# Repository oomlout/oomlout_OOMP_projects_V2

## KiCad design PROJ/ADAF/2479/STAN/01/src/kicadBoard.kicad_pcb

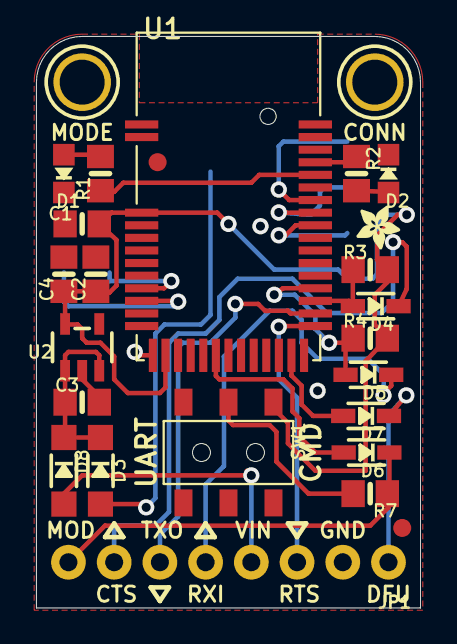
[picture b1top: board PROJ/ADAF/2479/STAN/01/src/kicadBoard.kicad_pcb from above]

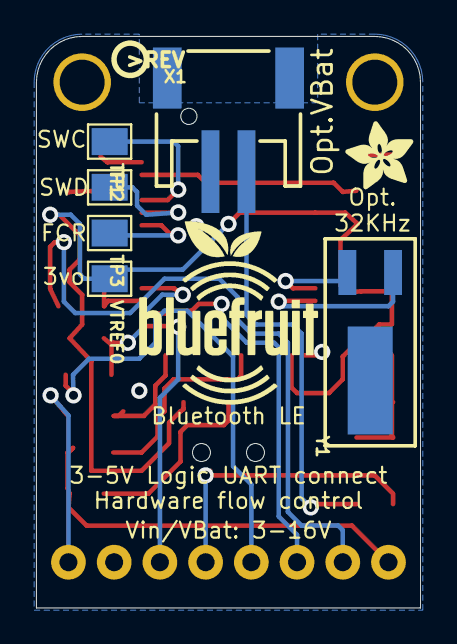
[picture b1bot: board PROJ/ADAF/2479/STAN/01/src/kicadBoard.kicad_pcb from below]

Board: 2 copper layers, 21.3 x 31.8 mm, 35 parts (9 on the bottom side), 25 nets.

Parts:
C1, C2: 1uF; 0805-NO
C3, C4: 10uF; 0805-NO
D1: RED; CHIPLED_0805_NOOUTLINE
D2: GREEN; CHIPLED_0805_NOOUTLINE
D3, D8: MBR120; SOD-123
D4, D5, D6, D7: 1n4148; SOD-323
FID1, FID2: FIDUCIAL""; FIDUCIAL_1MM
JP1: 1X08_ROUND_76
R1, R2: 1K; 0805-NO
R3, R4: 100K; 0805-NO
R7: 2K; 0805-NO
SW1: EG1319; EG1390
TP1: SWCLK; PAD-1.5X2.0
TP2: SWDIO; PAD-1.5X2.0
TP3: FCTRST; PAD-1.5X2.0
U1: BLE_MODULE_RAYTAC_MDBT40
U2: MIC5225-3.3; SOT23-5
U$9: BLUEFRUITLOGO_100MM
U$24: PCBFEAT-REV-040
U$25: ADAFRUIT_3.5MM
U$26: ADAFRUIT_2.5MM
U$28, U$29: MOUNTINGHOLE2.5; MOUNTINGHOLE_2.5_PLATED
VTREF0: FCTRST; PAD-1.5X2.0
X1: JST 2PH; JSTPH2
Y1: 32.768kHz (535-9166-2-ND); CRYSTAL_CYL_2X6MM_SMT

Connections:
3.3V: C1.1, C2.1, C4.1, R3.2, R4.2, SW1.O2, U1.3, U1.14, U2.5, VTREF0.P$1
CONNECTED_LED: R2.1, U1.39
CTS_3V: D4.A, R3.1, U1.28
CTS_5V: D4.C, JP1.7
DFU_3V: D7.A, U1.24
DFU_5V: D7.C, JP1.1
FCTRYRST_3V: TP3.P$1, U1.34
GND: C1.2, C2.2, C3.2, C4.2, D1.C, D2.C, JP1.2, SW1.S2, U1.1, U1.2, U1.13, U1.16, U1.25, U1.42, U2.2, X1.1
MODE_3V: D6.A, U1.18
MODE_5V: D6.C, JP1.8, R7.1
MODE_LED: R1.1, U1.38
unnamed: U1.9, Y1.1
unnamed: U1.10, Y1.2
unnamed: C3.1, D3.C, D8.C, U2.1, U2.3
unnamed: R7.2, SW1.P2
unnamed: D1.A, R1.2
unnamed: D2.A, R2.2
RTS_O: JP1.3, U1.26
RXD_3V: D5.A, R4.1, U1.29
RXD_5V: D5.C, JP1.5
SWCLK: TP1.P$1, U1.36
SWDIO/RST_3V: TP2.P$1, U1.35
TX_O: JP1.6, U1.27
VBAT: D3.A, X1.2
VIN: D8.A, JP1.4

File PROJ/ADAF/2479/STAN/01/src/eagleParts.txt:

Partlist

Exported from boardEagle.brd at 07/08/2022 18:05

EAGLE Version 9.6.2 Copyright (c) 1988-2020 Autodesk, Inc.

Assembly variant: 

Part     Value                     Package                  Library      Position (inch)       Orientation

C1       1uF                       0805-NO                  microbuilder (0.1 0.84)            R180
C2       1uF                       0805-NO                  microbuilder (0.13 0.73)           R90
C3       10uF                      0805-NO                  microbuilder (0.1 0.45)            R0
C4       10uF                      0805-NO                  microbuilder (0.06 0.73)           R90
D1       RED                       CHIPLED_0805_NOOUTLINE   microbuilder (0.06 0.95)           R180
D2       GREEN                     CHIPLED_0805_NOOUTLINE   microbuilder (0.77 0.95)           R0
D3       MBR120                    SOD-123                  microbuilder (0.14 0.3)            R270
D4       1n4148                    SOD-323                  microbuilder (0.742 0.66)          R180
D5       1n4148                    SOD-323                  microbuilder (0.726 0.51)          R180
D6       1n4148                    SOD-323                  microbuilder (0.722 0.34)          R180
D7       1n4148                    SOD-323                  microbuilder (0.721 0.42)          R180
D8       MBR120                    SOD-123                  microbuilder (0.06 0.3)            R270
FID1     FIDUCIAL""                FIDUCIAL_1MM             microbuilder (0.8 0.175)           R0
FID2     FIDUCIAL""                FIDUCIAL_1MM             microbuilder (0.265 0.975)         R0
JP1                                1X08_ROUND_76            microbuilder (0.42 0.1)            R180
R1       1K                        0805-NO                  microbuilder (0.14 0.95)           R90
R2       1K                        0805-NO                  microbuilder (0.7 0.95)            R270
R3       100K                      0805-NO                  microbuilder (0.73 0.74)           R0
R4       100K                      0805-NO                  microbuilder (0.73 0.59)           R0
R7       2K                        0805-NO                  microbuilder (0.73 0.25)           R180
SW1      EG1319                    EG1390                   microbuilder (0.42 0.34)           R180
TP1      SWCLK                     PAD-1.5X2.0              microbuilder (0.68 1.02)           MR270
TP2      SWDIO                     PAD-1.5X2.0              microbuilder (0.68 0.92)           MR90
TP3      FCTRST                    PAD-1.5X2.0              microbuilder (0.68 0.82)           MR270
U$28     MOUNTINGHOLE2.5           MOUNTINGHOLE_2.5_PLATED  microbuilder (0.74 1.15)           R0
U$29     MOUNTINGHOLE2.5           MOUNTINGHOLE_2.5_PLATED  microbuilder (0.1 1.15)            R0
U1                                 BLE_MODULE_RAYTAC_MDBT40 microbuilder (0.42 0.9)            R0
U2       MIC5225-3.3               SOT23-5                  microbuilder (0.1 0.57)            R0
VTREF    FCTRST                    PAD-1.5X2.0              microbuilder (0.68 0.72)           MR270
X1       JST 2PH                   JSTPH2                   microbuilder (0.42 1.1)            MR0
Y1       32.768kHz (535-9166-2-ND) CRYSTAL_CYL_2X6MM_SMT    microbuilder (0.11 0.65)           MR90

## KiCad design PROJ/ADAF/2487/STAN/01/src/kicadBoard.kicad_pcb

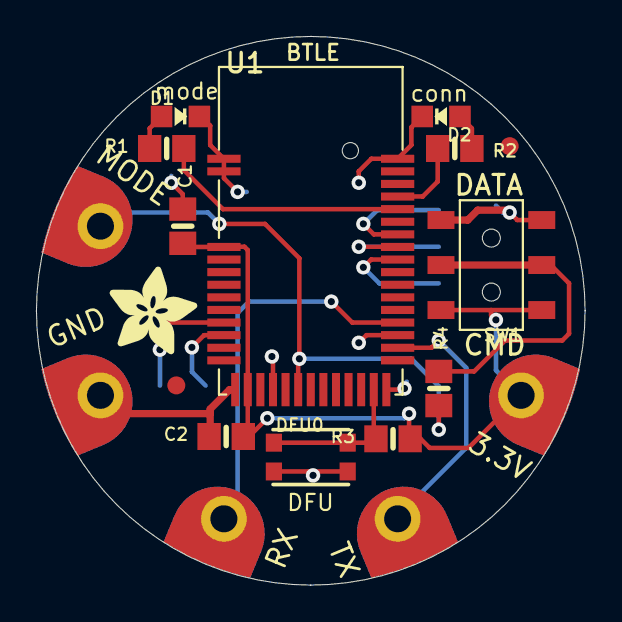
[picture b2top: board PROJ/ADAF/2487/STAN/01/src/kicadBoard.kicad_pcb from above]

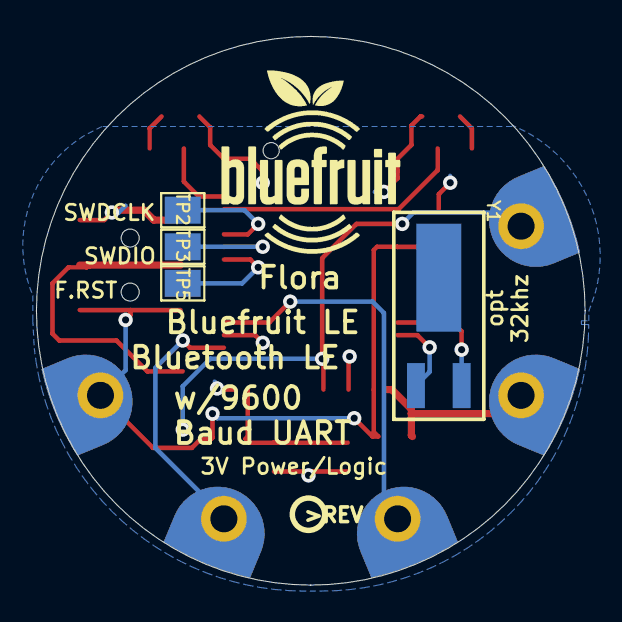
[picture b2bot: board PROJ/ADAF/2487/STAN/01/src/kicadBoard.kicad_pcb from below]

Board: 2 copper layers, 30.5 x 30.5 mm, 26 parts (7 on the bottom side), 16 nets.

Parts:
C1, C2: 1uF; 0805-NO
D1: RED; CHIPLED_0805_NOOUTLINE
D2: BLUE; CHIPLED_0805_NOOUTLINE
DFU0: KMR2; BTN_KMR2_4.6X2.8
FID1, FID2: FIDUCIAL""; FIDUCIAL_1MM
GND0: SEWTAP-2.0IN; SEWINGTAP_2.0
R1, R2, R4: 2K; 0805-NO
R3: 10K; 0805-NO
RX0: SEWTAP-2.0IN; SEWINGTAP_2.0
SW1: EG1319; EG1390
TP1: SEWTAP-2.0IN; SEWINGTAP_2.0
TP2: SWCLK; PAD-1.5X2.0
TP3: SWDIO; PAD-1.5X2.0
TP5: FCTRST; PAD-1.5X2.0
TX0: SEWTAP-2.0IN; SEWINGTAP_2.0
U1: MBT40; BLE_MODULE_RAYTAC_MDBT40
U$6: ADAFRUIT_5MM
U$7: FLORASMALL
U$23: BLUEFRUITLOGO_100MM
U$24: PCBFEAT-REV-040
UNK3V3IN0: SEWTAP-2.0IN; SEWINGTAP_2.0
Y1: 32.768kHz (535-9166-2-ND); CRYSTAL_CYL_2X6MM_SMT

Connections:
3.3V: C1.1, C2.1, R3.1, SW1.O1, SW1.O2, U1.3, U1.14, UNK3V3IN0.P$1
CONN_LED: R2.1, U1.39
DFU: DFU0.A, DFU0.A', R3.2, U1.24
FCTRYRST_3V: TP5.P$1, U1.34
GND: C1.2, C2.2, D1.C, D2.C, DFU0.B, DFU0.B', GND0.P$1, SW1.S1, SW1.S2, U1.1, U1.2, U1.13, U1.16, U1.25, U1.28, U1.42
MODE: R4.1, TP1.P$1, U1.18
MODE_LED: R1.1, U1.38
unnamed: R4.2, SW1.P1, SW1.P2
unnamed: D1.A, R1.2
unnamed: D2.A, R2.2
unnamed: U1.9, Y1.1
unnamed: U1.10, Y1.2
RXI: RX0.P$1, U1.29
SWCLK: TP2.P$1, U1.36
SWDIO/RST_3V: TP3.P$1, U1.35
TXO: TX0.P$1, U1.27

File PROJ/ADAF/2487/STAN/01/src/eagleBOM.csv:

"Part";"Value";"Device";"Package";"Description";"BOM";
"3V3IN";"SEWTAP-2.0IN";"SEWTAP-2.0IN";"SEWINGTAP_2.0";"";"";
"C1";"1uF";"CAP_CERAMIC0805-NOOUTLINE";"0805-NO";"Ceramic Capacitors";"";
"C2";"1uF";"CAP_CERAMIC0805-NOOUTLINE";"0805-NO";"Ceramic Capacitors";"";
"D1";"RED";"LED0805_NOOUTLINE";"CHIPLED_0805_NOOUTLINE";"LED";"";
"D2";"BLUE";"LED0805_NOOUTLINE";"CHIPLED_0805_NOOUTLINE";"LED";"";
"DFU";"KMR2";"SWITCH_TACT_SMT4.6X2.8";"BTN_KMR2_4.6X2.8";"SMT Tact Switches";"";
"FID1";"FIDUCIAL""";"FIDUCIAL""";"FIDUCIAL_1MM";"Fiducial Alignment Points";"EXCLUDE";
"FID2";"FIDUCIAL""";"FIDUCIAL""";"FIDUCIAL_1MM";"Fiducial Alignment Points";"EXCLUDE";
"GND";"SEWTAP-2.0IN";"SEWTAP-2.0IN";"SEWINGTAP_2.0";"";"";
"R1";"2K";"RESISTOR0805_NOOUTLINE";"0805-NO";"Resistors";"";
"R2";"2K";"RESISTOR0805_NOOUTLINE";"0805-NO";"Resistors";"";
"R3";"10K";"RESISTOR0805_NOOUTLINE";"0805-NO";"Resistors";"";
"R4";"2K";"RESISTOR0805_NOOUTLINE";"0805-NO";"Resistors";"";
"RX";"SEWTAP-2.0IN";"SEWTAP-2.0IN";"SEWINGTAP_2.0";"";"";
"SW1";"EG1319";"SWITCH_DPDTEG1390";"EG1390";"Switch - DPDT";"";
"TP1";"SEWTAP-2.0IN";"SEWTAP-2.0IN";"SEWINGTAP_2.0";"";"";
"TP2";"SWCLK";"TESTPOINT1.5X2.0MM_NOCREAM";"PAD-1.5X2.0";"Test Point";"";
"TP3";"SWDIO";"TESTPOINT1.5X2.0MM_NOCREAM";"PAD-1.5X2.0";"Test Point";"";
"TP5";"FCTRST";"TESTPOINT1.5X2.0MM_NOCREAM";"PAD-1.5X2.0";"Test Point";"";
"TX";"SEWTAP-2.0IN";"SEWTAP-2.0IN";"SEWINGTAP_2.0";"";"";
"U1";"MBT40";"NRF51822_MODULE_MDBT40";"BLE_MODULE_RAYTAC_MDBT40";"nRF51822 Bluetooth Low Energy Module";"";
"Y1";"32.768kHz (535-9166-2-ND)";"CRYSTAL2.0X6.0_32.768";"CRYSTAL_CYL_2X6MM_SMT";"Crystals";"";

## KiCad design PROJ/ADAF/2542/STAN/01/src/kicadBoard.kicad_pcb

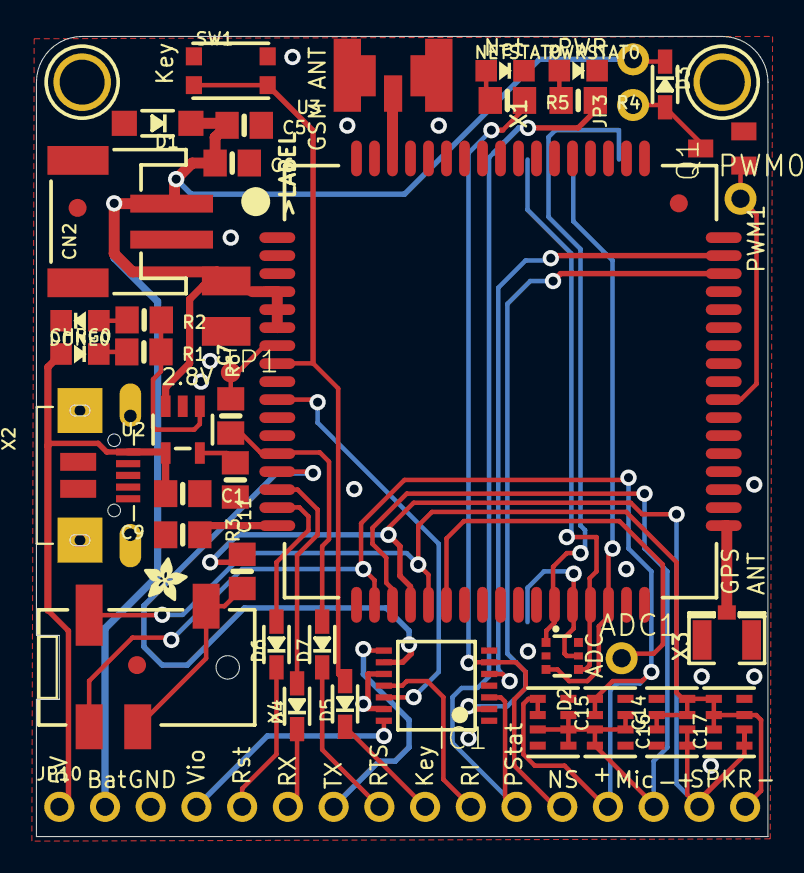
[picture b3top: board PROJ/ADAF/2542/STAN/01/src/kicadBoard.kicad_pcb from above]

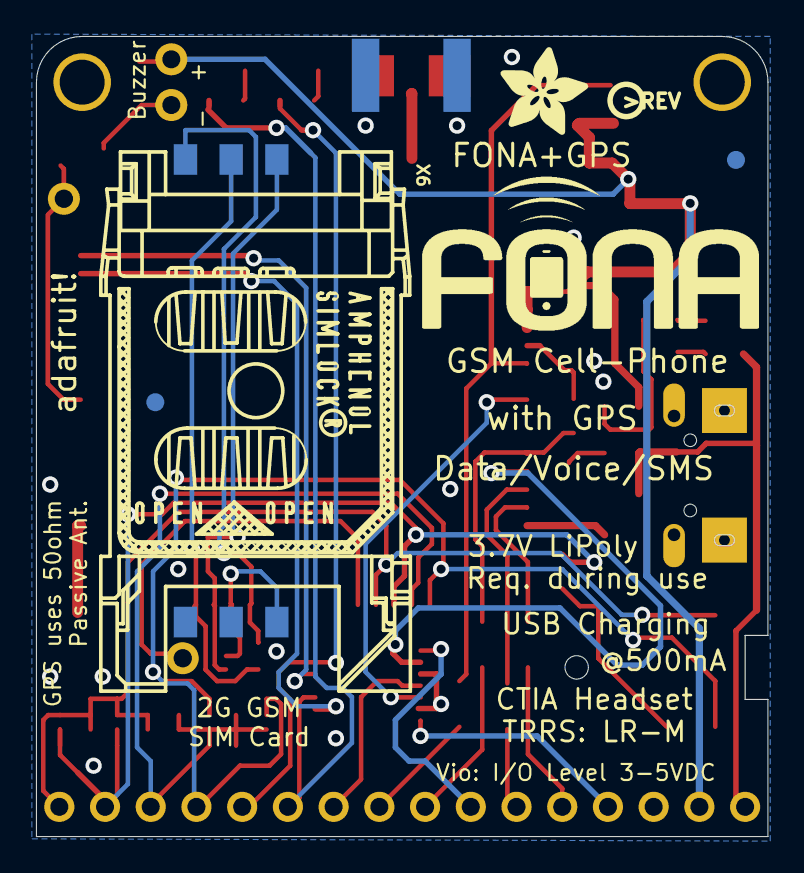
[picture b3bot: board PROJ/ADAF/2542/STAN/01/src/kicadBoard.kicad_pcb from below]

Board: 2 copper layers, 40.6 x 44.5 mm, 54 parts (6 on the bottom side), 42 nets.

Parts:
ADC1: 1X01-CLEANBIG
C1: 10µF; 0805-NO
C5: 10pF; 0805-NO
C6: 33pF; 0805-NO
C7: 100uF; C1210
C9, C11: 10uF; 0805-NO
C14, C16: 33pF; RESPACK_4X0603
C15, C17: 10pF; RESPACK_4X0603
CHRG0: ORANGE; CHIPLED_0805_NOOUTLINE
CN2: JSTPH; JSTPH2
D1: MMSZ5231BT1G; SOD-123
D2: SMF05C; SOT363
D3, D4, D5, D6, D7: 1N4148; SOD-323
DONE0: GREEN; CHIPLED_0805_NOOUTLINE
FID1, FID2, FID3, FID4, FID5: FIDUCIAL""; FIDUCIAL_1MM
IC1: 74VHCT125PW; TSSOP14
JP3: BUZZ; 1X02_ROUND
JP10: 1X16_ROUND
NETSTAT0: RED; CHIPLED_0805_NOOUTLINE
PWM0: 1X01-CLEANBIG
PWRSTAT0: BLUE; CHIPLED_0805_NOOUTLINE
Q1: DTC143ZUAT106; SC59-BEC
R1: 470; 0805-NO
R2, R4, R5: 1K; 0805-NO
R3: 2K; 0805-NO
R6: 10K; 0805-NO
SW1: KMR2; BTN_KMR2_4.6X2.8
TP1: TPTP11R; TP11R
U2: MCP73831T-2ACI/OT; SOT23-5
U3: SIM808; SIM900_SMT
U$21: ADAFRUIT_2.5MM
U$25: PCBFEAT-REV-040
U$26: FONA_LOGO
U$33, U$34: MOUNTINGHOLE2.5; MOUNTINGHOLE_2.5_PLATED
U$36: ADAFRUIT_5MM
X1: uFL; SMA_EDGELAUNCH_UFL
X2: MicroB; 4UCONN_20329
X3: uFL; U.FL
X4: 4UCONN_18510
X6: SIM_LOCKAMPHENOL; C707_10M006_512_2

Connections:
1.8V: D2.1, U3.P$29, X6.C1
2.8V: R6.2, TP1.TP, U3.P$7
+5V: C1.1, CHRG0.A, JP10.1, U2.4, X2.VBUS
GND: C1.2, C5.2, C6.2, C7.2, C9.2, C14.5, C14.8, C15.4, C15.8, C16.5, C16.8, C17.4, C17.8, CN2.1, D1.A, D2.2, DONE0.C, IC1.1, IC1.4, IC1.7, IC1.10, IC1.13, JP10.3, NETSTAT0.C, PWRSTAT0.C, Q1.E, R3.2, SW1.A, SW1.A', U2.2, U3.P$1, U3.P$2, U3.P$3, U3.P$18, U3.P$28, U3.P$34, U3.P$36, U3.P$40, U3.P$51, U3.P$52, U3.P$54, U3.P$64, U3.P$65, U3.P$67, U3.P$68, X1.GND@1, X1.GND@2, X1.GND@3, X1.GND@4, X2.BASE@1, X2.BASE@2, X2.GND, X2.SPRT@1, X2.SPRT@2, X2.SPRT@3, X2.SPRT@4, X3.1, X3.2, X6.C5
GSM_ANT: U3.P$66, X1.P
HP+: C11.1, X4.2-TIP, X4.3-OUTER_SLEEVE
MIC1+: C14.1, C14.2, C15.1, C15.2, JP10.13, U3.P$19, X4.1-GND
MIC1-: C14.3, C14.4, C14.6, C14.7, C15.3, C15.5, C15.6, C15.7, JP10.14, U3.P$20
unnamed: CHRG0.C, R1.1
unnamed: R1.2, R2.2, U2.1
unnamed: U3.P$35, X3.3
unnamed: PWRSTAT0.A, R4.1
unnamed: R3.1, U2.5
unnamed: DONE0.A, R2.1
unnamed: ADC1.1, U3.P$23
unnamed: NETSTAT0.A, R5.1
unnamed: D3.A, JP3.1, Q1.C
NETSTAT: IC1.5, U3.P$50
NETSTAT_5V: IC1.6, JP10.12, R5.2
PWM1: PWM0.1, Q1.B, U3.P$42
PWRKEY: D5.A, SW1.B, SW1.B', U3.P$8
PWRKEY_5V: D5.C, JP10.9
PWRSTAT: IC1.2, U3.P$49
PWRSTAT_5V: IC1.3, JP10.11, R4.2
RESET: D6.A, U3.P$16
RESET_5V: D6.C, JP10.5
RI: IC1.12, U3.P$10
RI_5V: IC1.11, JP10.10
RTS: D7.A, R6.1, U3.P$13
RTS_5V: D7.C, JP10.8
RXD_5V: D4.C, JP10.6
SIMCLK: D2.4, U3.P$31, X6.C3
SIMDATA: D2.5, U3.P$30, X6.C7
SIMRST: D2.3, U3.P$32, X6.C2
SPEAKER1+: C11.2, C16.1, C16.2, C17.1, C17.2, JP10.15, U3.P$21
SPEAKER1-: C16.3, C16.4, C16.6, C16.7, C17.3, C17.5, C17.6, C17.7, JP10.16, U3.P$22, X4.4-INNER_SLEEVE
TXD_5V: IC1.8, JP10.7
UART_RXD: D4.A, U3.P$15
UART_TXD: IC1.9, U3.P$14
VBAT: C5.1, C6.1, C7.1, CN2.2, D1.C, D3.C, JP3.2, JP10.2, U2.3, U3.P$4, U3.P$5, U3.P$6
VCCIO: IC1.14, JP10.4
VRTC: C9.1, U3.P$17

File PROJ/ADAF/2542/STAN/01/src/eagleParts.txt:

Partlist

Exported from boardEagle.brd at 07/08/2022 18:14

EAGLE Version 9.6.2 Copyright (c) 1988-2020 Autodesk, Inc.

Assembly variant: 

Part     Value             Package                 Library      Position (inch)       Orientation

ADC1                       1X01-CLEANBIG           adafruit     (1.28 0.39)           R0
C1       10µF              0805-NO                 microbuilder (0.32 0.75)           R0
C5       10pF              0805-NO                 microbuilder (0.45437008 1.55559055) R0
C6       33pF              0805-NO                 microbuilder (0.42814961 1.47311024) R0
C7       100uF             C1210                   rcl          (0.415 1.16)          R270
C9       10uF              0805-NO                 microbuilder (0.32 0.66)           R180
C11      10uF              0805-NO                 microbuilder (0.45 0.58)           R90
C14      33pF              RESPACK_4X0603          microbuilder (1.255 0.25)          R270
C15      10pF              RESPACK_4X0603          microbuilder (1.13 0.25)           R270
C16      33pF              RESPACK_4X0603          microbuilder (1.39 0.25)           R90
C17      10pF              RESPACK_4X0603          microbuilder (1.515 0.25)          R90
CHRG     ORANGE            CHIPLED_0805_NOOUTLINE  microbuilder (0.09503937 1.05543307) R270
CN2      JSTPH             JSTPH2                  microbuilder (0.15 1.345)          R90
D1       MMSZ5231BT1G      SOD-123                 microbuilder (0.265 1.56)          R180
D2       SMF05C            SOT363                  microbuilder (1.15 0.395)          R270
D3       1N4148            SOD-323                 microbuilder (1.375 1.645)         R270
D4       1N4148            SOD-323                 microbuilder (0.57 0.285)          R90
D5       1N4148            SOD-323                 microbuilder (0.675 0.29)          R90
D6       1N4148            SOD-323                 microbuilder (0.525 0.42)          R90
D7       1N4148            SOD-323                 microbuilder (0.625 0.42)          R90
DONE     GREEN             CHIPLED_0805_NOOUTLINE  microbuilder (0.09523622 1.12818898) R90
FID1     FIDUCIAL""        FIDUCIAL_1MM            microbuilder (1.405 1.385)         R0
FID2     FIDUCIAL""        FIDUCIAL_1MM            microbuilder (0.09 1.375)          R0
FID3     FIDUCIAL""        FIDUCIAL_1MM            microbuilder (0.22 0.375)          R0
FID4     FIDUCIAL""        FIDUCIAL_1MM            microbuilder (0.07 1.48)           MR0
FID5     FIDUCIAL""        FIDUCIAL_1MM            microbuilder (1.34 0.95)           MR0
IC1      74VHCT125PW       TSSOP14                 74xx-us      (0.875 0.33)          R90
JP3      BUZZ              1X02_ROUND              microbuilder (1.305 1.65)          R90
JP10                       1X16_ROUND              microbuilder (0.8 0.065)           R0
NETSTAT  RED               CHIPLED_0805_NOOUTLINE  microbuilder (1.025 1.675)         R270
PWM                        1X01-CLEANBIG           adafruit     (1.54 1.395)          R0
PWRSTAT  BLUE              CHIPLED_0805_NOOUTLINE  microbuilder (1.185 1.675)         R270
Q1       DTC143ZUAT106     SC59-BEC                transistor   (1.5 1.505)           R90
R1       470               0805-NO                 microbuilder (0.235 1.06)          R0
R2       1K                0805-NO                 microbuilder (0.23562992 1.13)     R0
R3       2K                0805-NO                 microbuilder (0.435 0.78)          R270
R4       1K                0805-NO                 microbuilder (1.185 1.61)          R0
R5       1K                0805-NO                 microbuilder (1.03 1.61)           R0
R6       10K               0805-NO                 microbuilder (0.425 0.92)          R90
SW1      KMR2              BTN_KMR2_4.6X2.8        microbuilder (0.425 1.675)         R0
TP1      TPTP11R           TP11R                   testpad      (0.425 1.015)         R0
U$33     MOUNTINGHOLE2.5   MOUNTINGHOLE_2.5_PLATED microbuilder (1.5 1.65)            R90
U$34     MOUNTINGHOLE2.5   MOUNTINGHOLE_2.5_PLATED microbuilder (0.1 1.65)            R90
U2       MCP73831T-2ACI/OT SOT23-5                 microbuilder (0.32 0.89)           R180
U3       SIM808            SIM900_SMT              microbuilder (1.015 0.995)         R0
X1       uFL               SMA_EDGELAUNCH_UFL      microbuilder (0.78 1.745)          R270
X2       MicroB            4UCONN_20329            microbuilder (0.17 0.79)           R270
X3       uFL               U.FL                    microbuilder (1.51 0.43)           R90
X4       4UCONN_18510      4UCONN_18510            microbuilder (0.005 0.37)          R0
X6       SIM_LOCKAMPHENOL  C707_10M006_512_2       microbuilder (1.12 0.975)          MR270

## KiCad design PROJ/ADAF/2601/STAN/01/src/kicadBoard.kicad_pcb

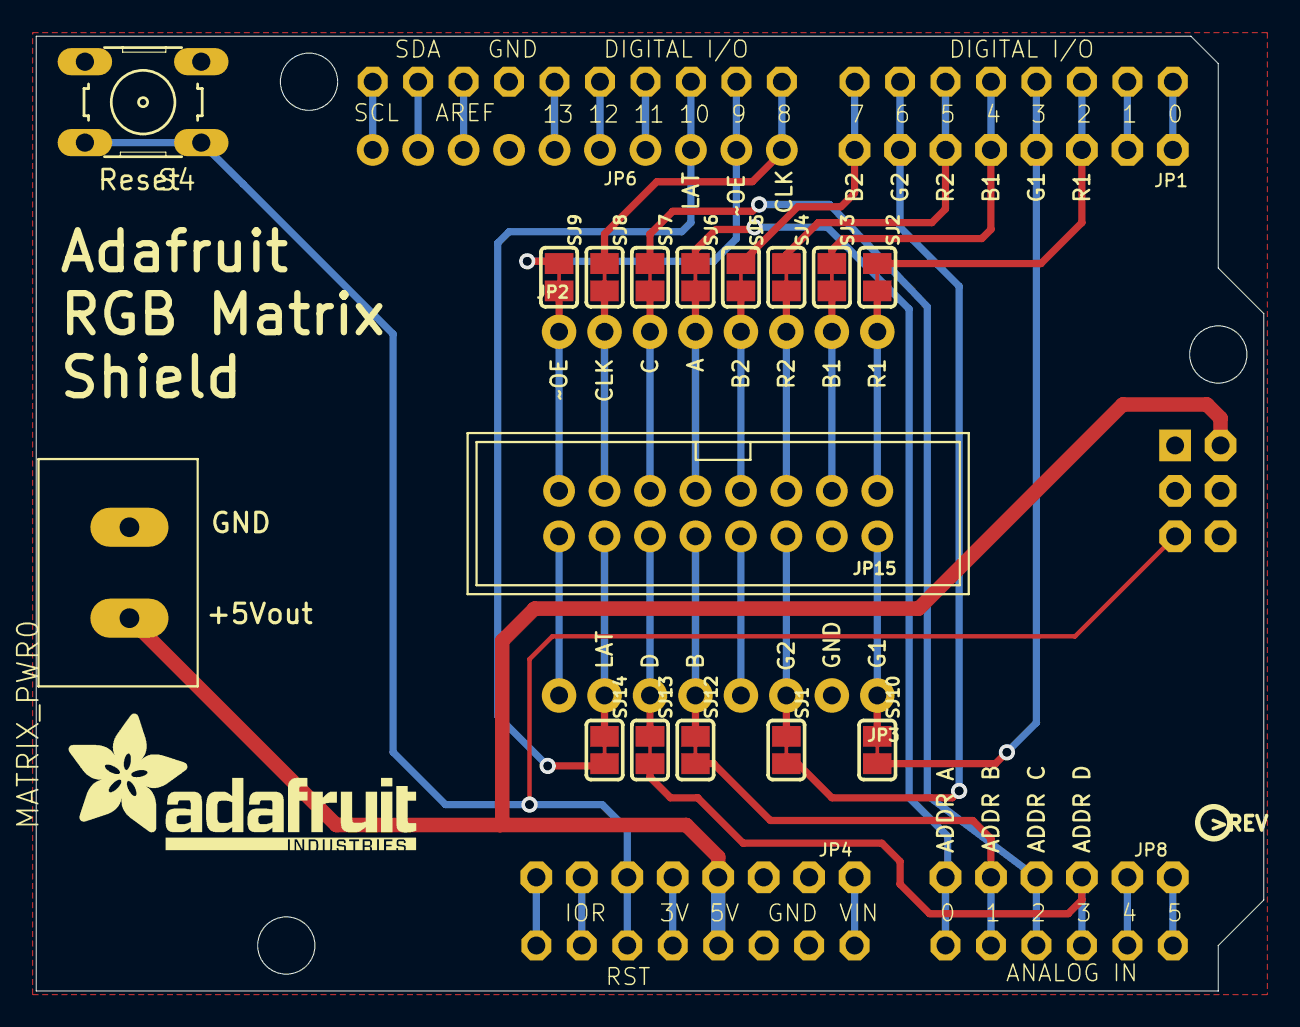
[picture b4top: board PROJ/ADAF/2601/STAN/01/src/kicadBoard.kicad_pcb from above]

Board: 2 copper layers, 68.6 x 53.3 mm, 28 parts (0 on the bottom side), 45 nets.

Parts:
@HOLE0, @HOLE1, @HOLE2: (no value)
JP1, JP4: 1X08-CLEANBIG
JP2, JP3: 1X08_ROUND_76
JP6: 1X10_ROUND70
JP8: 1X06-CLEANBIG
JP15: Shrouded 2x8; 2X08_SHROUDED
MATRIX_PWR0: PINHEAD; TERMBLOCK508
S4: 6mm; B3F-10XX
SJ1, SJ2, SJ3, SJ4, SJ5, SJ6, SJ7, SJ8, SJ9, SJ10, SJ12, SJ13, SJ14: SOLDERJUMPER_CLOSEDWIRE
U$8: PCBFEAT-REV-040
U$9: ADAFRUIT_TEXT_20MM
U$41: ARDUINO_R3_ICSP_NODIM; ARDUINOR3_ICSP_NODIM

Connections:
+3V: JP4.5, U$41.3V
+5V: JP4.4, MATRIX_PWR0.P$4, U$41.5V, U$41.5V_ICSP
A0: JP8.6, SJ6.1, U$41.A0
A1: JP8.5, SJ12.2, U$41.A1
A2: JP8.4, SJ7.1, U$41.A2
A3: JP8.3, SJ13.2, U$41.A3
A4: JP8.2, U$41.A4
A5: JP8.1, U$41.A5
ADDR_A: JP2.4, JP15.9, SJ6.2
ADDR_B: JP3.5, JP15.10, SJ12.1
ADDR_C: JP2.3, JP15.11, SJ7.2
ADDR_D: JP3.6, JP15.12, SJ13.1
AREF: JP6.3, U$41.AREF
B1: JP2.7, JP15.3, SJ3.2
B2: JP2.5, JP15.7, SJ5.2
CLK: JP2.2, JP15.13, SJ8.2
D0: JP1.8, U$41.D0
D1: JP1.7, U$41.D1
D2: JP1.6, SJ2.1, U$41.D2
D3: JP1.5, SJ10.2, U$41.D3
D4: JP1.4, SJ3.1, U$41.D4
D5: JP1.3, SJ4.1, U$41.D5
D6: JP1.2, SJ1.2, U$41.D6
D7: JP1.1, SJ5.1, U$41.D7
D8: JP6.10, SJ8.1, U$41.D8
D9: JP6.9, SJ9.1, U$41.D9
D10: JP6.8, SJ14.2, U$41.D10
D11: JP6.7, U$41.D11
D12: JP6.6, U$41.D12
D13: JP6.5, U$41.D13
E_1: JP3.4, JP15.8
E_2: JP3.8, JP15.16
G1: JP3.1, JP15.2, SJ10.1
G2: JP3.3, JP15.6, SJ1.1
GND: JP3.2, JP4.2, JP4.3, JP6.4, JP15.4, MATRIX_PWR0.P$3, S4.3, S4.4, U$41.GND, U$41.GND@1, U$41.GND@2, U$41.GND@3
IOREF: JP4.7, U$41.IOREF
LAT: JP3.7, JP15.14, SJ14.1
NC: JP4.8, U$41.RESERVED
OE: JP2.1, JP15.15, SJ9.2
R1: JP2.8, JP15.1, SJ2.2
R2: JP2.6, JP15.5, SJ4.2
SCL: JP6.1, U$41.SCL
SDA: JP6.2, U$41.SDA
VIN: JP4.1, U$41.VIN
~RESET: JP4.6, S4.1, S4.2, U$41.RESET, U$41.RESET_ICSP

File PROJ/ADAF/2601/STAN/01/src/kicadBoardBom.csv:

"Id";"Designator";"Package";"Quantity";"Designation";"Supplier and ref";
1;"SJ13,SJ12,SJ1,SJ5,SJ6,SJ7,SJ3,SJ10,SJ2,SJ4,SJ9,SJ14,SJ8";"SOLDERJUMPER_CLOSEDWIRE";13;"";;;
2;"@HOLE0,@HOLE2,@HOLE1";"";3;"";;;
3;"JP1,JP4";"1X08-CLEANBIG";2;"";;;
4;"MATRIX_PWR0";"TERMBLOCK508";1;"PINHEAD";;;
5;"U$8";"PCBFEAT-REV-040";1;"";;;
6;"JP6";"1X10_ROUND70";1;"";;;
7;"JP15";"2X08_SHROUDED";1;"Shrouded 2x8";;;
8;"JP2,JP3";"1X08_ROUND_76";2;"";;;
9;"S4";"B3F-10XX";1;"6mm";;;
10;"U$41";"ARDUINOR3_ICSP_NODIM";1;"ARDUINO_R3_ICSP_NODIM";;;
11;"U$9";"ADAFRUIT_TEXT_20MM";1;"";;;
12;"JP8";"1X06-CLEANBIG";1;"";;;

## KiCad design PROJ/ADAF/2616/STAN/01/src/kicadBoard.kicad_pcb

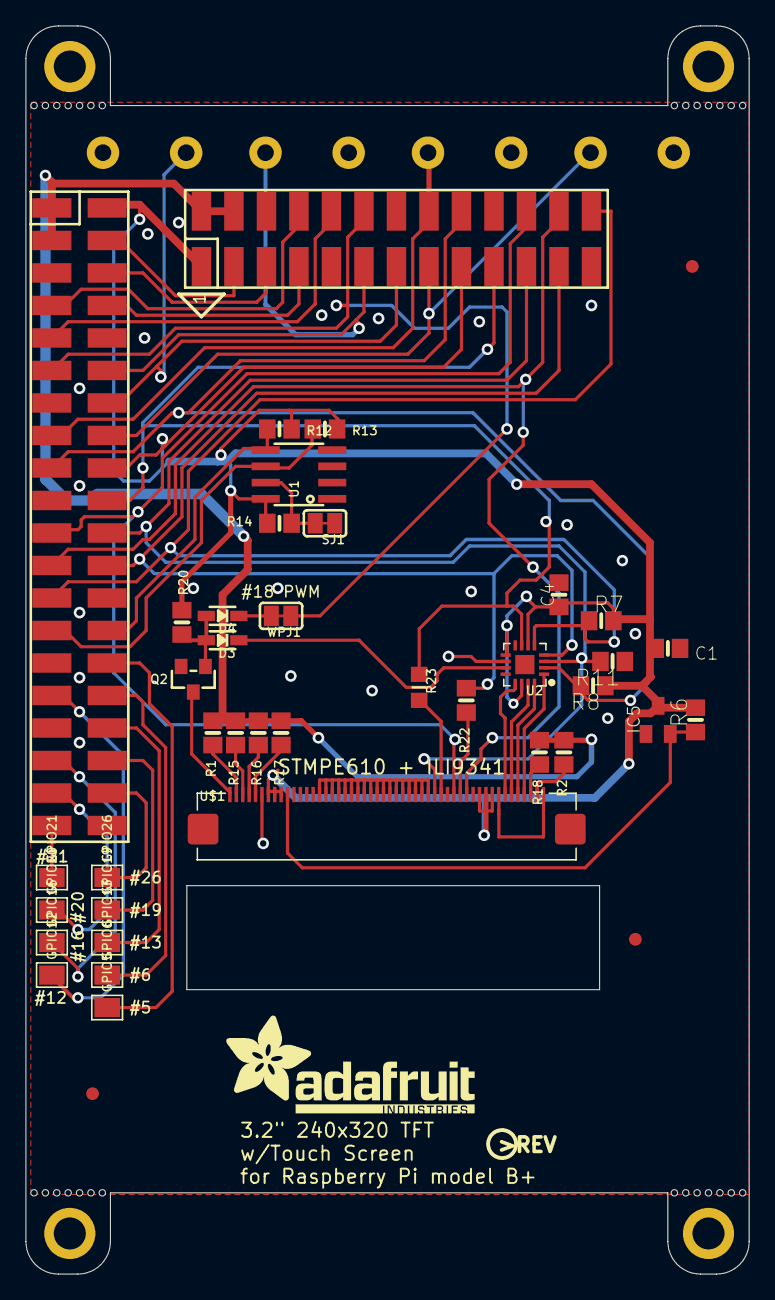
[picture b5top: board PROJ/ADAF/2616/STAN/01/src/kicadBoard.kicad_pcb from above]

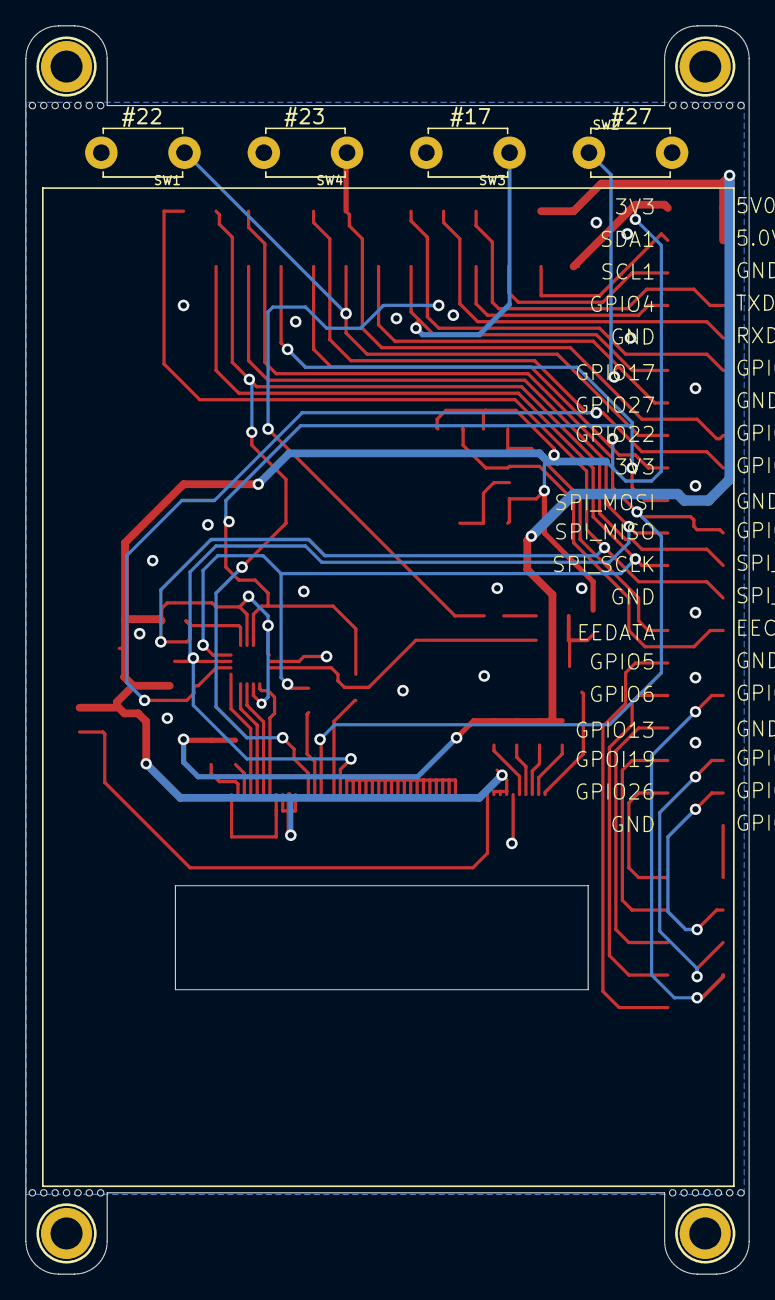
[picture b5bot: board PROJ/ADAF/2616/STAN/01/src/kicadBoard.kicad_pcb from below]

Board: 16 copper layers, 56.5 x 97.5 mm, 79 parts (10 on the bottom side), 50 nets.

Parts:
@HOLE0, @HOLE1, @HOLE2, @HOLE3, @HOLE4, @HOLE5, @HOLE6, @HOLE7, @HOLE8, @HOLE9, @HOLE10, @HOLE11, @HOLE12, @HOLE13, @HOLE14, @HOLE15, @HOLE16, @HOLE17, @HOLE18, @HOLE19, @HOLE20, @HOLE21, @HOLE22, @HOLE23, @HOLE24, @HOLE25, @HOLE26, @HOLE27: (no value)
C1: 10uF; 0805-NO
C4: 0.1uF; 0805-NO
D3, D4: 1N4148; SOD-323
GPIO5, GPIO6, GPIO12, GPIO13, GPIO16, GPIO19, GPIO20, GPIO21, GPIO26: PAD-1.5X2.0
IC5: AXP803; SOT23
JP1: 2X13_SMT_MALE
Q2: BSS138; SOT23-WIDE
R1, R2, R15, R16, R17, R18: 100; 0805-NO
R6, R7, R11: 10K; 0805-NO
R8: DNP; 0805-NO
R12, R13, R14, R20: 3.9K; 0805-NO
R22: 22; 0805-NO
R23: 22; _0805MP
RPI1: RASPBERRYPI_BPLUS_SMT; RASPBERRYPI_BPLUS_SHIELD_SMT
SJ1: WP; SOLDERJUMPER_CLOSEDWIRE
SW1, SW2, SW3, SW4: TACT_PANA-EVQ
U1: CAT24C32; SOIC8_150MIL
U2: STMPE610; QFN16_3MM
U$1: DISP_LCD_6LED_240X320_50PIN; TFT_3.2IN_240X320_50PIN
U$10, U$11, U$18: FIDUCIAL""; FIDUCIAL_1MM
U$15, U$16, U$17, U$20: MOUNTINGHOLE2.5_THICK; MOUNTINGHOLE_2.5_PLATED_THICK
U$19: PCBFEAT-REV-056
U$23: ADAFRUIT_TEXT_20MM
WPJ1: SOLDERJUMPER_CLOSEDWIRE

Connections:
3.3V: C1.1, C4.1, IC5.3, JP1.1, JP1.17, R6.2, R7.2, R8.1, R12.2, R13.2, R14.2, R20.2, RPI1.1, RPI1.17, U1.8, U2.6, U2.9, U2.14, U$1.7, U$1.8, U$1.9, U$1.40, U$1.41, U$1.42
+5V: JP1.2, JP1.4, R1.1, R2.1, R15.1, R16.1, R17.1, R18.1, RPI1.2, RPI1.4
EECLK: R13.1, RPI1.28, U1.6
EEDATA: R12.1, RPI1.27, U1.5
GND: C1.2, C4.2, IC5.1, JP1.6, JP1.9, JP1.14, JP1.20, JP1.25, Q2.2, R11.1, RPI1.6, RPI1.9, RPI1.14, RPI1.20, RPI1.25, RPI1.30, RPI1.34, RPI1.39, SJ1.1, SW1.P$2, SW2.P$2, SW3.P$2, SW4.P$2, U1.1, U1.2, U1.3, U1.4, U2.10, U$1.6, U$1.43, U$1.50
GPIO6: GPIO6.P$1, RPI1.31
GPIO16: GPIO16.P$1, RPI1.36
GPIO17: JP1.11, RPI1.11, SW3.P$1
GPIO18: JP1.12, RPI1.12, WPJ1.1
GPIO22: JP1.15, RPI1.15, SW1.P$1
GPIO23: JP1.16, RPI1.16, SW4.P$1
GPIO27: JP1.13, RPI1.13, SW2.P$1
MISO: JP1.21, R11.2, RPI1.21, U2.3, U$1.33
MOSI: JP1.19, R23.1, RPI1.19, U2.7
unnamed: R2.2, U$1.49
unnamed: R1.2, U$1.2
unnamed: D3.C, U2.11
unnamed: GPIO5.P$1, RPI1.29
unnamed: JP1.3, RPI1.3
unnamed: JP1.5, RPI1.5
unnamed: JP1.7, RPI1.7
unnamed: GPIO13.P$1, RPI1.33
unnamed: GPIO19.P$1, RPI1.35
unnamed: GPIO26.P$1, RPI1.37
unnamed: GPIO12.P$1, RPI1.32
unnamed: GPIO20.P$1, RPI1.38
unnamed: R14.1, SJ1.2, U1.7
unnamed: JP1.10, RPI1.10
unnamed: JP1.8, RPI1.8
unnamed: GPIO21.P$1, RPI1.40
unnamed: D3.A, D4.A, Q2.1, R20.1
unnamed: U$1.15, U$1.16, U$1.17, U$1.18, U$1.19, U$1.20, U$1.21, U$1.22, U$1.23, U$1.24, U$1.25, U$1.26, U$1.27, U$1.28, U$1.29, U$1.30, U$1.31, U$1.32
unnamed: Q2.3, U$1.1
unnamed: R15.2, U$1.3
unnamed: R16.2, U$1.4
unnamed: R17.2, U$1.5
unnamed: R18.2, U$1.48
unnamed: D4.C, WPJ1.2
RT_CS: JP1.26, R7.1, RPI1.26, U2.5
RT_INT: JP1.18, R8.2, RPI1.18, U2.2
SCLK: JP1.23, R22.1, RPI1.23, U2.4
SDI: R23.2, U$1.34
SPICLK: R22.2, U$1.37
TFT_CS: JP1.24, RPI1.24, U$1.38
TFT_DC: JP1.22, RPI1.22, U$1.36
TFT_RST: IC5.2, R6.1, U$1.10
XL: U2.16, U$1.46
XR: U2.13, U$1.44
YD: U2.15, U$1.45
YU: U2.1, U$1.47

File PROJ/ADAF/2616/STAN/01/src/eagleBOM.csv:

"Part";"Value";"Device";"Package";"Description";"BOM";
"C1";"10uF";"CAP_CERAMIC0805-NOOUTLINE";"0805-NO";"Ceramic Capacitors";"";
"C4";"0.1uF";"CAP_CERAMIC0805-NOOUTLINE";"0805-NO";"Ceramic Capacitors";"";
"D3";"1N4148";"DIODESOD-323";"SOD-323";"Diode";"";
"D4";"1N4148";"DIODESOD-323";"SOD-323";"Diode";"";
"GPIO5";"";"TESTPOINT1.5X2.0MM_NOCREAM";"PAD-1.5X2.0";"Test Point";"";
"GPIO6";"";"TESTPOINT1.5X2.0MM_NOCREAM";"PAD-1.5X2.0";"Test Point";"";
"GPIO12";"";"TESTPOINT1.5X2.0MM_NOCREAM";"PAD-1.5X2.0";"Test Point";"";
"GPIO13";"";"TESTPOINT1.5X2.0MM_NOCREAM";"PAD-1.5X2.0";"Test Point";"";
"GPIO16";"";"TESTPOINT1.5X2.0MM_NOCREAM";"PAD-1.5X2.0";"Test Point";"";
"GPIO19";"";"TESTPOINT1.5X2.0MM_NOCREAM";"PAD-1.5X2.0";"Test Point";"";
"GPIO20";"";"TESTPOINT1.5X2.0MM_NOCREAM";"PAD-1.5X2.0";"Test Point";"";
"GPIO21";"";"TESTPOINT1.5X2.0MM_NOCREAM";"PAD-1.5X2.0";"Test Point";"";
"GPIO26";"";"TESTPOINT1.5X2.0MM_NOCREAM";"PAD-1.5X2.0";"Test Point";"";
"IC5";"AXP803";"AXP083-SAG";"SOT23";"";"";
"JP1";"";"HEADER-2X13-SMT";"2X13_SMT_MALE";"";"";
"Q2";"BSS138";"MOSFET-NWIDE";"SOT23-WIDE";"N-Channel Mosfet";"";
"R1";"100";"RESISTOR0805_NOOUTLINE";"0805-NO";"Resistors";"";
"R2";"100";"RESISTOR0805_NOOUTLINE";"0805-NO";"Resistors";"";
"R6";"10K";"RESISTOR0805_NOOUTLINE";"0805-NO";"Resistors";"";
"R7";"10K";"RESISTOR0805_NOOUTLINE";"0805-NO";"Resistors";"";
"R8";"DNP";"RESISTOR0805_NOOUTLINE";"0805-NO";"Resistors";"";
"R11";"10K";"RESISTOR0805_NOOUTLINE";"0805-NO";"Resistors";"";
"R12";"3.9K";"RESISTOR0805_NOOUTLINE";"0805-NO";"Resistors";"";
"R13";"3.9K";"RESISTOR0805_NOOUTLINE";"0805-NO";"Resistors";"";
"R14";"3.9K";"RESISTOR0805_NOOUTLINE";"0805-NO";"Resistors";"";
"R15";"100";"RESISTOR0805_NOOUTLINE";"0805-NO";"Resistors";"";
"R16";"100";"RESISTOR0805_NOOUTLINE";"0805-NO";"Resistors";"";
"R17";"100";"RESISTOR0805_NOOUTLINE";"0805-NO";"Resistors";"";
"R18";"100";"RESISTOR0805_NOOUTLINE";"0805-NO";"Resistors";"";
"R20";"3.9K";"RESISTOR0805_NOOUTLINE";"0805-NO";"Resistors";"";
"R22";"22";"RESISTOR0805_NOOUTLINE";"0805-NO";"Resistors";"";
"R23";"22";"RESISTOR_0805MP";"_0805MP";"Resistors";"";
"RPI1";"RASPBERRYPI_BPLUS_SMT";"RASPBERRYPI_BPLUS_SMT";"RASPBERRYPI_BPLUS_SHIELD_SMT";"";"";
"SJ1";"WP";"SOLDERJUMPER_CLOSED";"SOLDERJUMPER_CLOSEDWIRE";"Solder Jumper - Closed";"";
"SW1";"";"SWITCH_PUSHBUTTONEVQ-PE";"TACT_PANA-EVQ";"Buttons";"";
"SW2";"";"SWITCH_PUSHBUTTONEVQ-PE";"TACT_PANA-EVQ";"Buttons";"";
"SW3";"";"SWITCH_PUSHBUTTONEVQ-PE";"TACT_PANA-EVQ";"Buttons";"";
"SW4";"";"SWITCH_PUSHBUTTONEVQ-PE";"TACT_PANA-EVQ";"Buttons";"";
"U$1";"DISP_LCD_6LED_240X320_50PIN";"DISP_LCD_6LED_240X320_50PIN";"TFT_3.2IN_240X320_50PIN";"";"";
"U$10";"FIDUCIAL""";"FIDUCIAL""";"FIDUCIAL_1MM";"Fiducial Alignment Points";"EXCLUDE";
"U$11";"FIDUCIAL""";"FIDUCIAL""";"FIDUCIAL_1MM";"Fiducial Alignment Points";"EXCLUDE";
"U$15";"MOUNTINGHOLE2.5_THICK";"MOUNTINGHOLE2.5_THICK";"MOUNTINGHOLE_2.5_PLATED_THICK";"Mounting Hole";"EXCLUDE";
"U$16";"MOUNTINGHOLE2.5_THICK";"MOUNTINGHOLE2.5_THICK";"MOUNTINGHOLE_2.5_PLATED_THICK";"Mounting Hole";"EXCLUDE";
"U$17";"MOUNTINGHOLE2.5_THICK";"MOUNTINGHOLE2.5_THICK";"MOUNTINGHOLE_2.5_PLATED_THICK";"Mounting Hole";"EXCLUDE";
"U$18";"FIDUCIAL""";"FIDUCIAL""";"FIDUCIAL_1MM";"Fiducial Alignment Points";"EXCLUDE";
"U$20";"MOUNTINGHOLE2.5_THICK";"MOUNTINGHOLE2.5_THICK";"MOUNTINGHOLE_2.5_PLATED_THICK";"Mounting Hole";"EXCLUDE";
"U1";"CAT24C32";"EEPROM_I2C_SOIC8_GENERIC";"SOIC8_150MIL";"Note: The same pinout is used for many I2C EEPROMs in SOIC8(150mil) from a variety of manufacturers and in various sizes.";"";
"U2";"STMPE610";"STMPE610";"QFN16_3MM";"STMPE610 - 12-Bit Touch Screen Controller";"";
"WPJ1";"";"SOLDERJUMPERCLOSED";"SOLDERJUMPER_CLOSEDWIRE";"SMD Solder JUMPER";"";

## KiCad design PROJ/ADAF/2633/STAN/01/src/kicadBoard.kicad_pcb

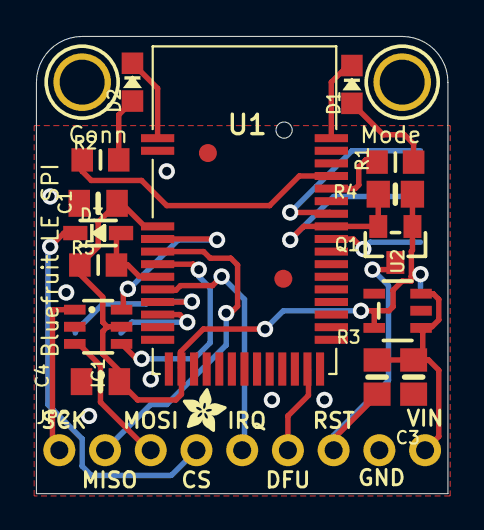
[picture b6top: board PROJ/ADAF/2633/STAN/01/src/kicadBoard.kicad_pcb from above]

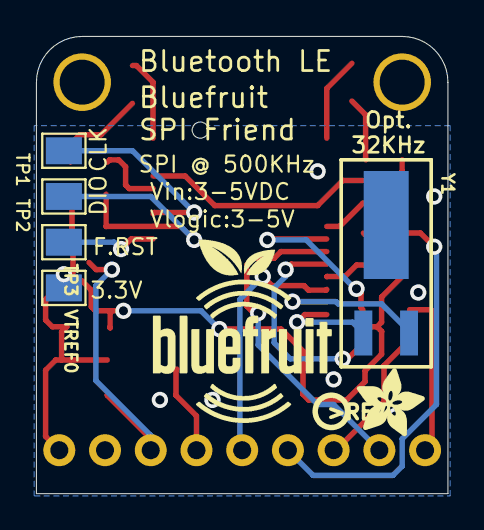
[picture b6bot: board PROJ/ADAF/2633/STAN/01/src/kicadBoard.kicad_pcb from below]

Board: 2 copper layers, 22.9 x 25.4 mm, 29 parts (8 on the bottom side), 22 nets.

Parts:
C1: 1uF; 0805_10MGAP
C3: 10uF; 0805-NO
C4: 10uF; 0805_10MGAP
D1: RED; CHIPLED_0805_NOOUTLINE
D2: BLUE; CHIPLED_0805_NOOUTLINE
D3: 1N4148; SOD-323
FID1, FID3: FIDUCIAL""; FIDUCIAL_1MM
IC1: 74LVC2G34DBVR; SOT23-6
JP2: 1X09_ROUND_70
Q1: BSS138; SOT23-WIDE@1
R1, R2: 2K; _0805MP
R3, R4: 100K; 0805-NO
R5: 100K; _0805MP
TP1: SWCLK; PAD-1.5X2.0
TP2: SWDIO; PAD-1.5X2.0
TP3: FCTRST; PAD-1.5X2.0
U1: 32KB NRF51822; BLE_MODULE_RAYTAC_MDBT40
U2: MIC5225-3.3; SOT23-5
U$3: ADAFRUIT_2.5MM
U$9: BLUEFRUITLOGO_100MM
U$17: ADAFRUIT_3.5MM
U$18: PCBFEAT-REV-040
U$28, U$29: MOUNTINGHOLE2.5; MOUNTINGHOLE_2.5_PLATED
VTREF0: THREEV; PAD-1.5X2.0
Y1: 32.768kHz (535-9166-2-ND); CRYSTAL_CYL_2X6MM_SMT

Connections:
3.3V: C1.1, C4.1, IC1.5, Q1.1, R4.1, R5.1, U1.3, U1.14, U2.5, VTREF0.P$1
CONNECTED: R2.1, U1.39
CS_3V: D3.A, R5.2, U1.7
CS_5V: D3.C, JP2.4
DFU_3V: JP2.6, U1.24
FACTORYRST: TP3.P$1, U1.34
GND: C1.2, C3.2, C4.2, D1.C, D2.C, IC1.2, JP2.8, U1.1, U1.2, U1.13, U1.16, U1.25, U1.42, U2.2
IRQ_3V: JP2.5, U1.8
MISO_3V: JP2.2, U1.5
MODE: R1.1, U1.38
MOSI_3V: IC1.4, U1.6
MOSI_5V: IC1.3, JP2.3
unnamed: U1.9, Y1.1
unnamed: U1.10, Y1.2
unnamed: D1.A, R1.2
unnamed: D2.A, R2.2
SCK_3V: IC1.6, U1.4
SCK_5V: IC1.1, JP2.1
SWCLK: TP1.P$1, U1.36
SWDIO/RST_3V: Q1.2, R4.2, TP2.P$1, U1.35
SWDIO/RST_5V: JP2.7, Q1.3, R3.2
VIN: C3.1, JP2.9, R3.1, U2.1, U2.3

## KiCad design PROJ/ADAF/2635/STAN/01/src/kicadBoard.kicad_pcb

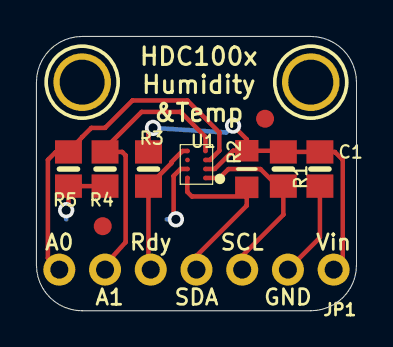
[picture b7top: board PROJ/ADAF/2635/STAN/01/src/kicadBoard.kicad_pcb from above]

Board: 2 copper layers, 17.8 x 15.2 mm, 13 parts (1 on the bottom side), 7 nets.

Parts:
C1: 10uF; 0805-NO
FID1, FID2: FIDUCIAL""; FIDUCIAL_1MM
JP1: 1X07_ROUND_70
R1, R3, R4, R5: 10K; 0805-NO
R2: 10K; _0805MP
U1: HDC1008; DSBGA8_HDC1008
U$2, U$3: MOUNTINGHOLE2.5; MOUNTINGHOLE_2.5_PLATED
U$14: ADAFRUIT_3.5MM

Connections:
A0: JP1.7, R5.2, U1.C1
A1: JP1.6, R4.2, U1.D1
GND: C1.2, JP1.2, R4.1, R5.1, U1.B2
RDY: JP1.5, R3.1, U1.D2
SCL: JP1.3, R1.1, U1.A1
SDY: JP1.4, R2.1, U1.A2
VDD: C1.1, JP1.1, R1.2, R2.2, R3.2, U1.B1
